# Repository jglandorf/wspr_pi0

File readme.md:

## RPi Zero W WSPR Amplifier

 - A 100mW+ HF transmit amplifier daughterboard for the Raspberry Pi Zero W
 - Direct connection of dipole antenna
 - Select one of two HF band low-pass filters via jumper.  30M LPF built-in; 2nd LPF user-supplied.
 - OLED direct plug-in
 - Part of the ARROW Communication Association (w8rp.org) Build Sessions, Aug 2019
 - See docs/wspr_pi0_assembly.pdf
 
 73 de Joe, AC8ES

https://github.com/jglandorf/wspr_pi0.git
https://github.com/jglandorf/wspr_pi0.git/docs
https://github.com/jglandorf/wspr_pi0.git/RPi0_usdCardImage

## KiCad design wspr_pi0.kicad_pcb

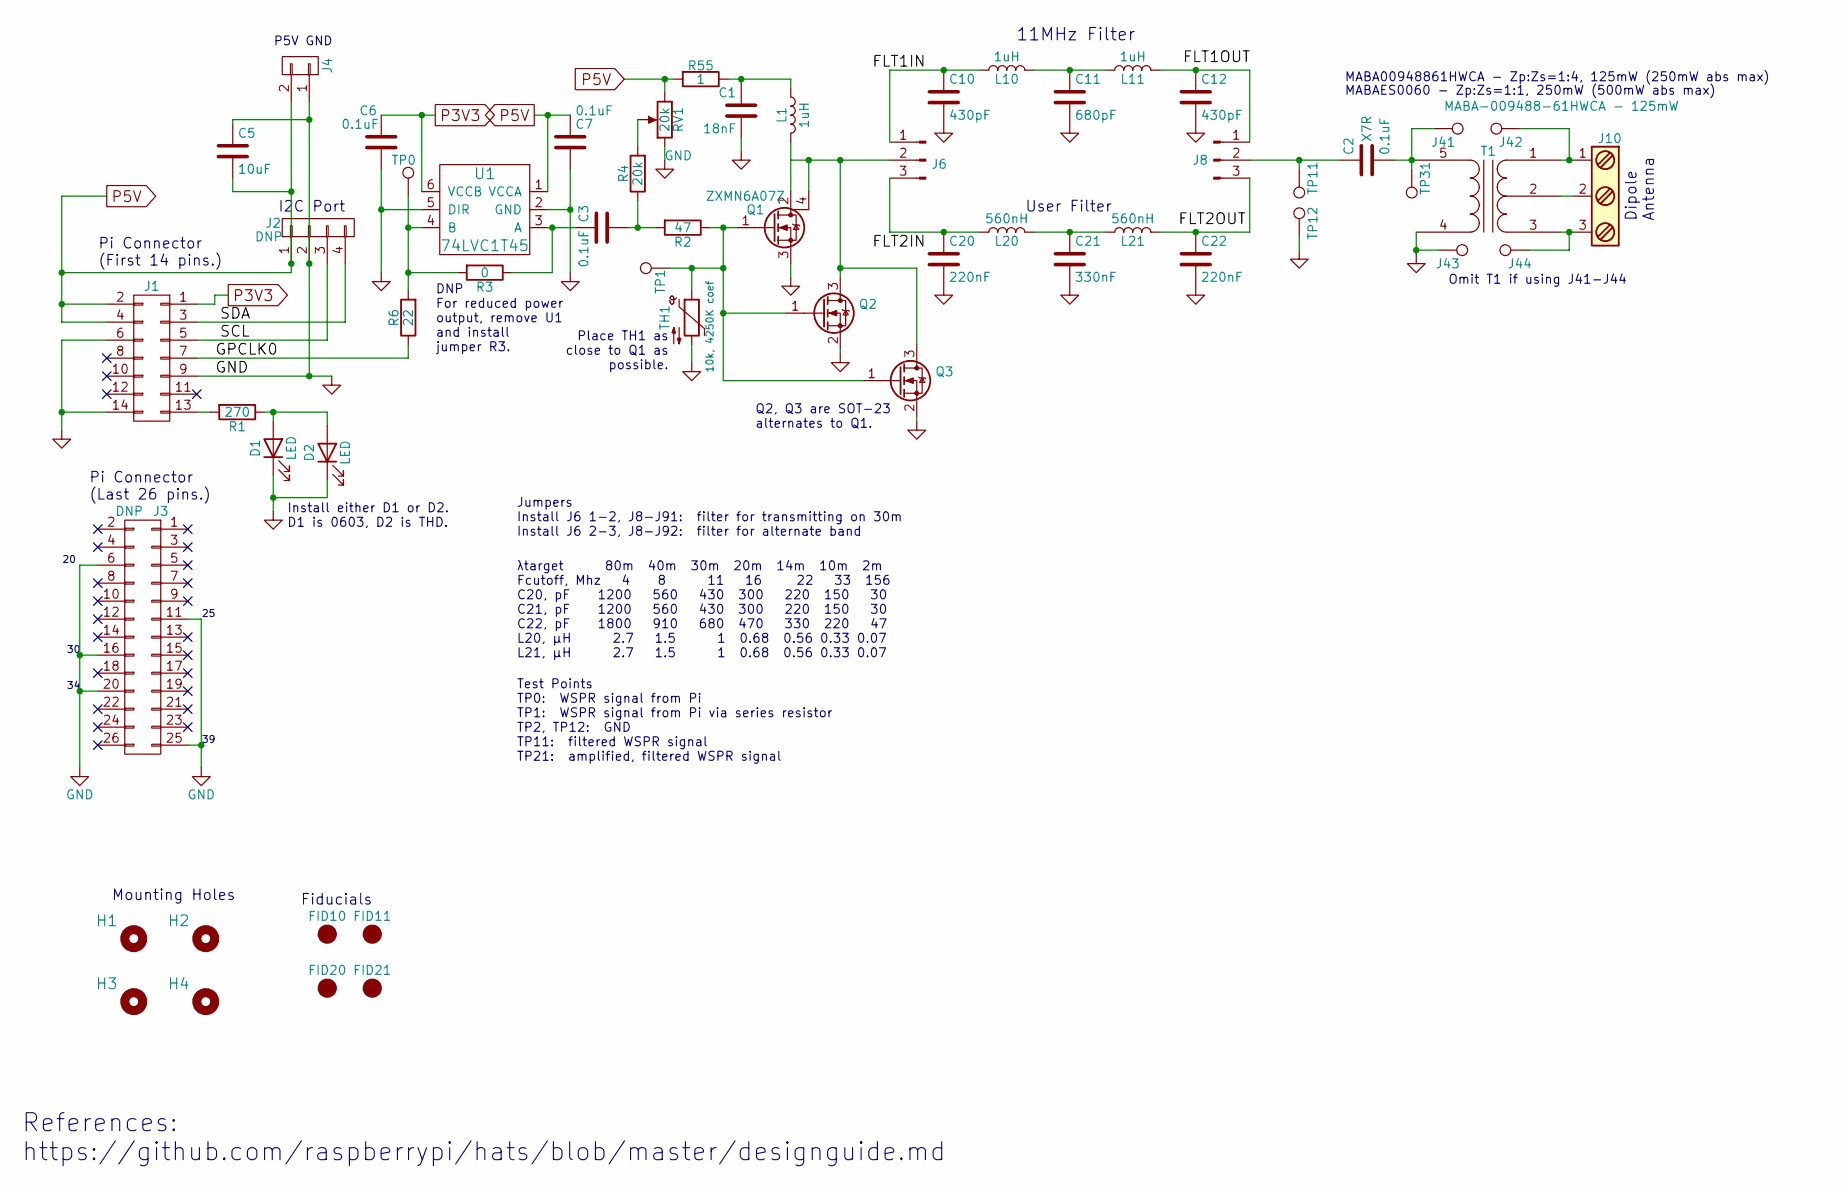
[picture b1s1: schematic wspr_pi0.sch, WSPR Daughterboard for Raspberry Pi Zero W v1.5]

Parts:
C1: 18nF; C_0603
C2, C3, C6, C7: 0.1uF; C_0603
C5: 10uF; C_0805_HandSoldering
C10, C12: 430pF; C_0603
C11: 680pF; C_0603
C20, C22: 220nF; C_Disc_D6.0mm_W4.4mm_P5.00mm; MPN FG28X7R1H224KRT06
C21: 330nF; C_Disc_D6.0mm_W4.4mm_P5.00mm; MPN FG28X7R1H334KRT06
D1: LED; LED_0603; MPN 19-217/R6C-AL1M2VY/3T
D2: LED; LED-3MM; MPN WP710A10LSRD
FID10, FID11: CIRCLE1mmDia; Fiducial_1mm_Dia_2.54mm_Outer_CopperTop; MPN DNP
FID20, FID21: CIRCLE1mmDia; Fiducial_1mm_Dia_2.54mm_Outer_CopperBottom; MPN DNP
H1, H2: 3mm_Mounting_Hole; NPTH_3mm_ID; MPN DNP
H3, H4: 3mm_Mounting_Hole_Unlocked; NPTH_3mm_ID_Unlocked; MPN DNP
J1: CONN_02X07; Pin_Header_Straight_2x07_Pitch2.54mm; MPN SFH11-PBPC-D07-ST-BK
J2: DNP; Pin_Header_Straight_1x04_Pitch2.54mm
J3: DNP; Pin_Header_Straight_2x13_Pitch2.54mm; MPN DNP
J4: CONN_01X02; Pin_Header_Straight_1x02
J6, J8: Conn_01x03_Male; PinHeader_1x03_P2.54mm_Vertical
J10: Screw_Terminal_1x03; TerminalBlock_Pheonix_MKDS1.5-3pol; MPN 0398800303
J41, J42, J43, J44: TEST_1P; Socket_Strip_Straight_1x01_Pitch2.54mm; MPN DNP
L1, L10, L11: 1uH; L_Axial_L11.0mm_D4.5mm_P5.08mm_Vertical_Fastron_MECC; MPN B78108S1102K000
L20, L21: 560nH; L_Axial_L7.0mm_D3.3mm_P10.16mm_Horizontal_Fastron_MICC; MPN 78FR56K-RC
Q1: ZXMN6A07Z; SOT89-3_MOSFET; MPN ZXMN6A07ZCT
Q2, Q3: DNP; SOT-23_Handsoldering; MPN IRLML2030TRPbF
R1: 270; R_0603; MPN RC0603JR-07270RL
R2: 47; R_0603; MPN RC0603JR-0747RL
R3: 0; R_0603_HandSoldering; MPN ERJ-3GEY0R00V
R4: 20k; R_0603
R6: 22; R_0603_HandSoldering
R55: 1; R_1206_HandSoldering
RV1: 20k; Potentiometer_Bourns_TC33X
T1: MABA-009488-61HWCA - 125mW; SO-BALUN-5_SMD; MPN MABA-009488-61HWCA
TH1: 10k, 4250K coef; R_0603_HandSoldering; MPN ERT-J1VR103J
TP0, TP1, TP11, TP12, TP31: TEST_1P; Pin_Header_Straight_1x01_Pitch1.27mm; MPN DNP
U1: 74LVC1T45; SOT-23-6_Handsoldering

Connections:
/GPCLK0: J1.7, R6.1
/SCL: J1.5, J2.3
/SDA: J1.3, J2.4
GND: C1.2, C5.1, C6.2, C7.2, C10.2, C11.2, C12.2, C20.2, C21.2, C22.2, D1.1 (K), D2.1 (K), J1.6, J1.9, J1.14, J2.2, J3.6, J3.11, J3.16, J3.20, J3.25, J4.1, J43.1, Q1.3 (S), Q2.2 (S), Q3.2 (S), RV1.1, T1.4 (PR1), TH1.2, TP12.1, U1.2 (GND), U1.5 (DIR)
unnamed: C1.1, L1.2, R55.1
unnamed: C2.1, J8.2, TP11.1
unnamed: C2.2, J41.1, T1.5 (PR2), TP31.1
unnamed: C3.1, R3.1, U1.3 (A)
unnamed: C3.2, R2.2, R4.1
unnamed: C10.1, J6.1, L10.1
unnamed: C11.1, L10.2, L11.1
unnamed: C12.1, J8.1, L11.2
unnamed: C20.1, J6.3, L20.1
unnamed: C21.1, L20.2, L21.1
unnamed: C22.1, J8.3, L21.2
unnamed: D1.2 (A), D2.2 (A), R1.1
unnamed: J1.13, R1.2
unnamed: J6.2, Q1.4 (D), Q2.3 (D), Q3.3 (D)
unnamed: J10.1, J42.1, T1.1 (S1)
unnamed: J10.2, T1.2 (SM)
unnamed: J10.3, J44.1, T1.3 (S2)
unnamed: L1.1, Q1.2 (D)
unnamed: Q1.1 (G), Q2.1 (G), Q3.1 (G), R2.1, TH1.1, TP1.1
unnamed: R3.2, R6.2, TP0.1, U1.4 (B)
unnamed: R4.2, RV1.2
P3V3: C6.1, J1.1, U1.6 (VCCB)
P5V: C5.2, C7.1, J1.2, J1.4, J2.1, J4.2, R55.2, RV1.3, U1.1 (VCCA)

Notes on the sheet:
Mounting Holes
Pi Connector (First 14 pins.)
References: https://github.com/raspberrypi/hats/blob/master/designguide.md
11MHz Filter
User Filter
I2C Port
Dipole Antenna
Pi Connector (Last 26 pins.)
Fiducials
MABA00948861HWCA - Zp:Zs=1:4, 125mW (250mW abs max)
MABAES0060 - Zp:Zs=1:1, 250mW (500mW abs max)
Jumpers Install J6 1-2, J8-J91: filter for transmitting on 30m Install J6 2-3, J8-J92: filter for alternate band
Test Points TP0: WSPR signal from Pi TP1: WSPR signal from Pi via series resistor TP2, TP12: GND TP11: filtered WSPR signal TP21: amplified, filtered WSPR signal
λtarget 80m 40m 30m 20m 14m 10m 2m Fcutoff, Mhz 4 8 11 16 22 33 156 C20, pF 1200 560 430 300 220 150 30 C21, pF 1200 560 430 300 220 150 30 C22, pF 1800 910 680 470 330 220 47 L20, μH 2.7 1.5 1 0.68 0.56 0.33 0.07 L21, μH 2.7 1.5 1 0.68 0.56 0.33 0.07
Omit T1 if using J41-J44
Install either D1 or D2. D1 is 0603, D2 is THD.
P5V GND
Place TH1 as close to Q1 as possible.
Q2, Q3 are SOT-23 alternates to Q1.
DNP For reduced power output, remove U1 and install jumper R3.

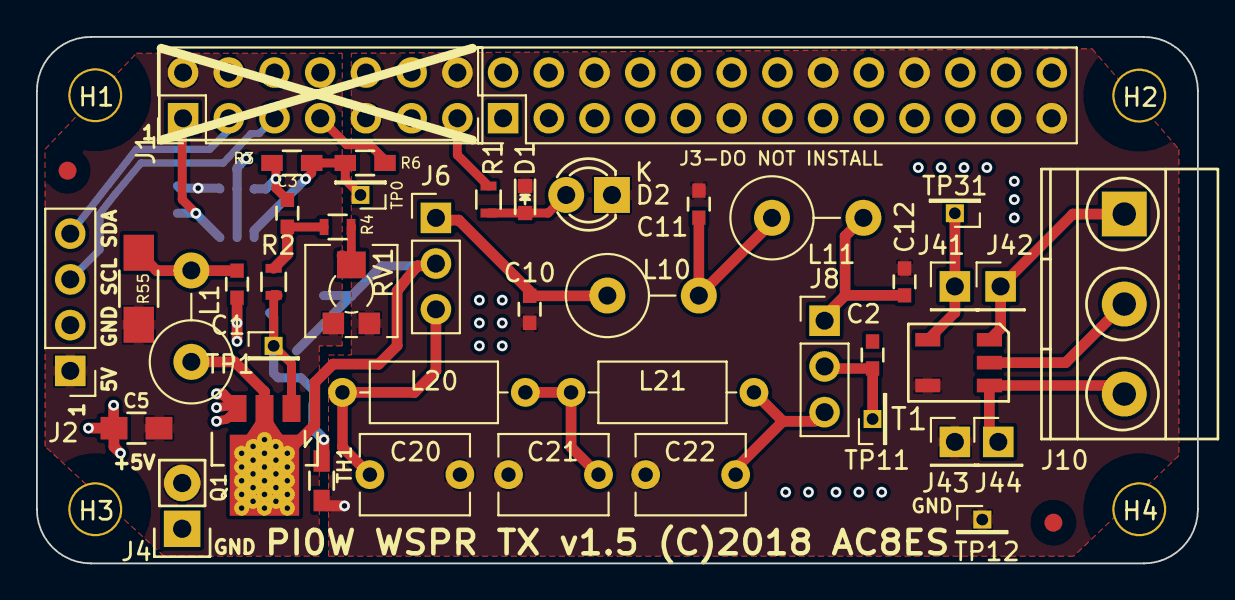
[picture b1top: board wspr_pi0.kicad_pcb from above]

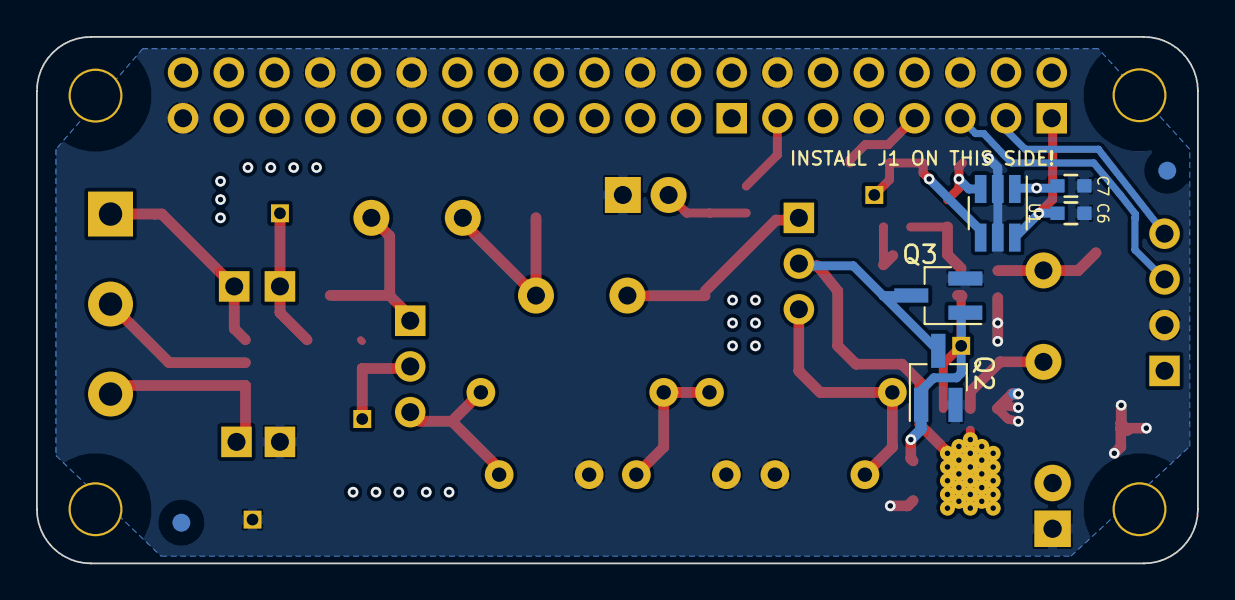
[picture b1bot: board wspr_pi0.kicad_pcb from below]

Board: 2 copper layers, 64.5 x 29.2 mm, 56 parts (5 on the bottom side), 27 nets.

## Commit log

2022-05-16 Initial commit.
2022-05-17 Add pdf versions of schematic and layout.

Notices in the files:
wspr_pi0.kicad_pcb:
PI0W WSPR TX v1.5 (C)2018 AC8ES
wspr_pi0.sch:
(C)2018-2019 AC8ES
